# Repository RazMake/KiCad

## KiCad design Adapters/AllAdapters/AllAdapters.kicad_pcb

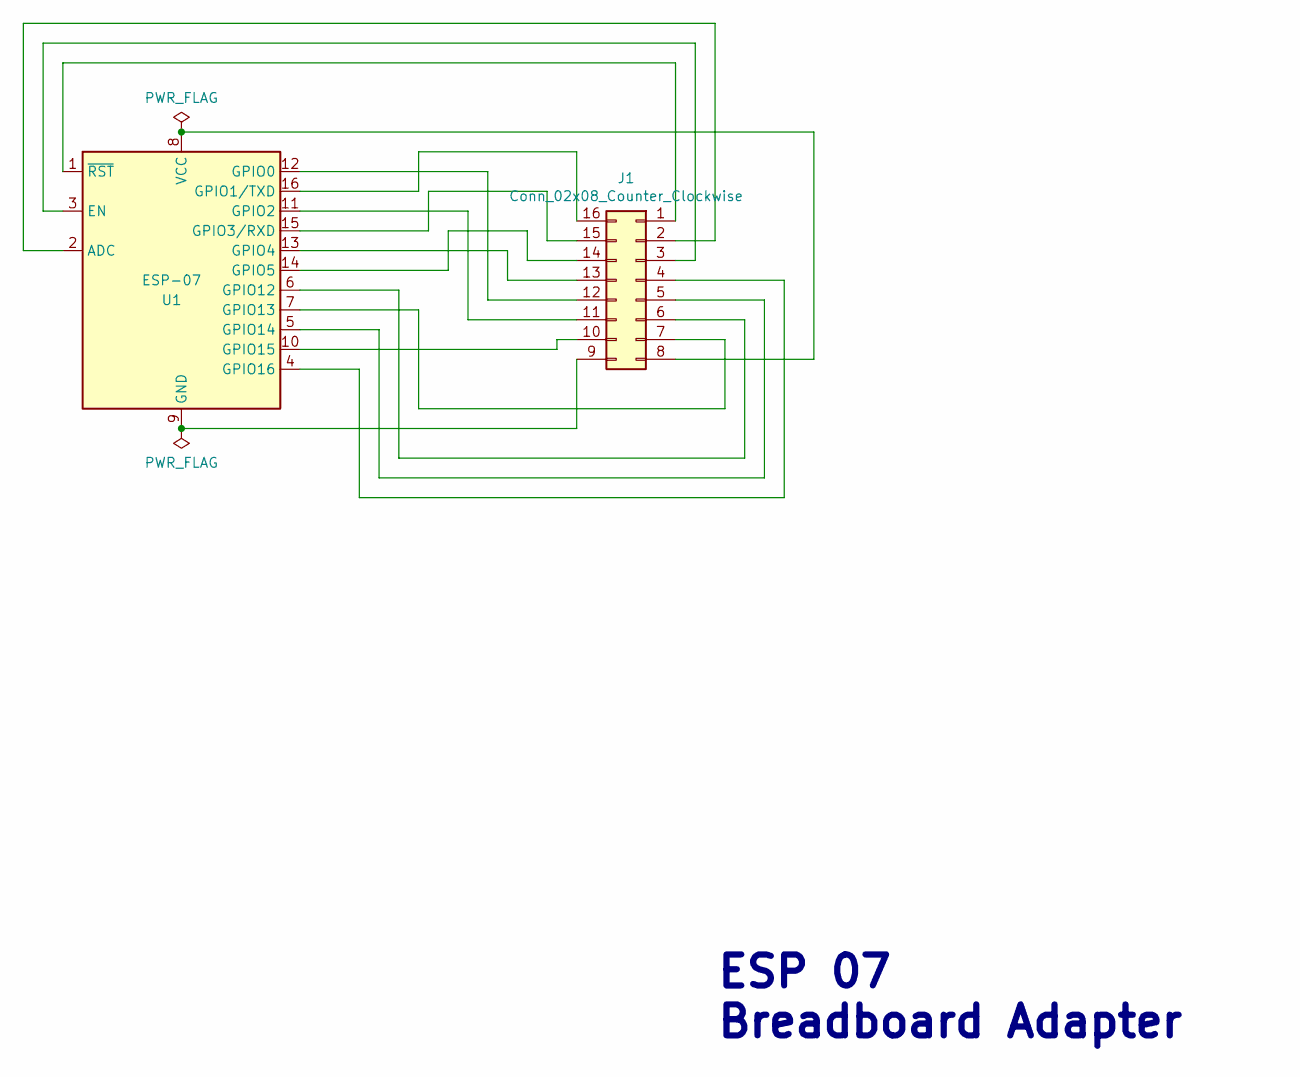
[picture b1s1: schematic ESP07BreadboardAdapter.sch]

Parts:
J1: Conn_02x08_Counter_Clockwise; ESP07BreaboardSocket
U1: ESP-07; ESP-07Socket

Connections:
unnamed: J1.1, U1.1 (~RST)
unnamed: J1.2, U1.2 (ADC)
unnamed: J1.3, U1.3 (EN)
unnamed: J1.4, U1.4 (GPIO16)
unnamed: J1.5, U1.5 (GPIO14)
unnamed: J1.6, U1.6 (GPIO12)
unnamed: J1.7, U1.7 (GPIO13)
unnamed: J1.8, U1.8 (VCC)
unnamed: J1.9, U1.9 (GND)
unnamed: J1.10, U1.10 (GPIO15)
unnamed: J1.11, U1.11 (GPIO2)
unnamed: J1.12, U1.12 (GPIO0)
unnamed: J1.13, U1.13 (GPIO4)
unnamed: J1.14, U1.14 (GPIO5)
unnamed: J1.15, U1.15 (GPIO3/RXD)
unnamed: J1.16, U1.16 (GPIO1/TXD)

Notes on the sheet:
ESP 07 Breadboard Adapter

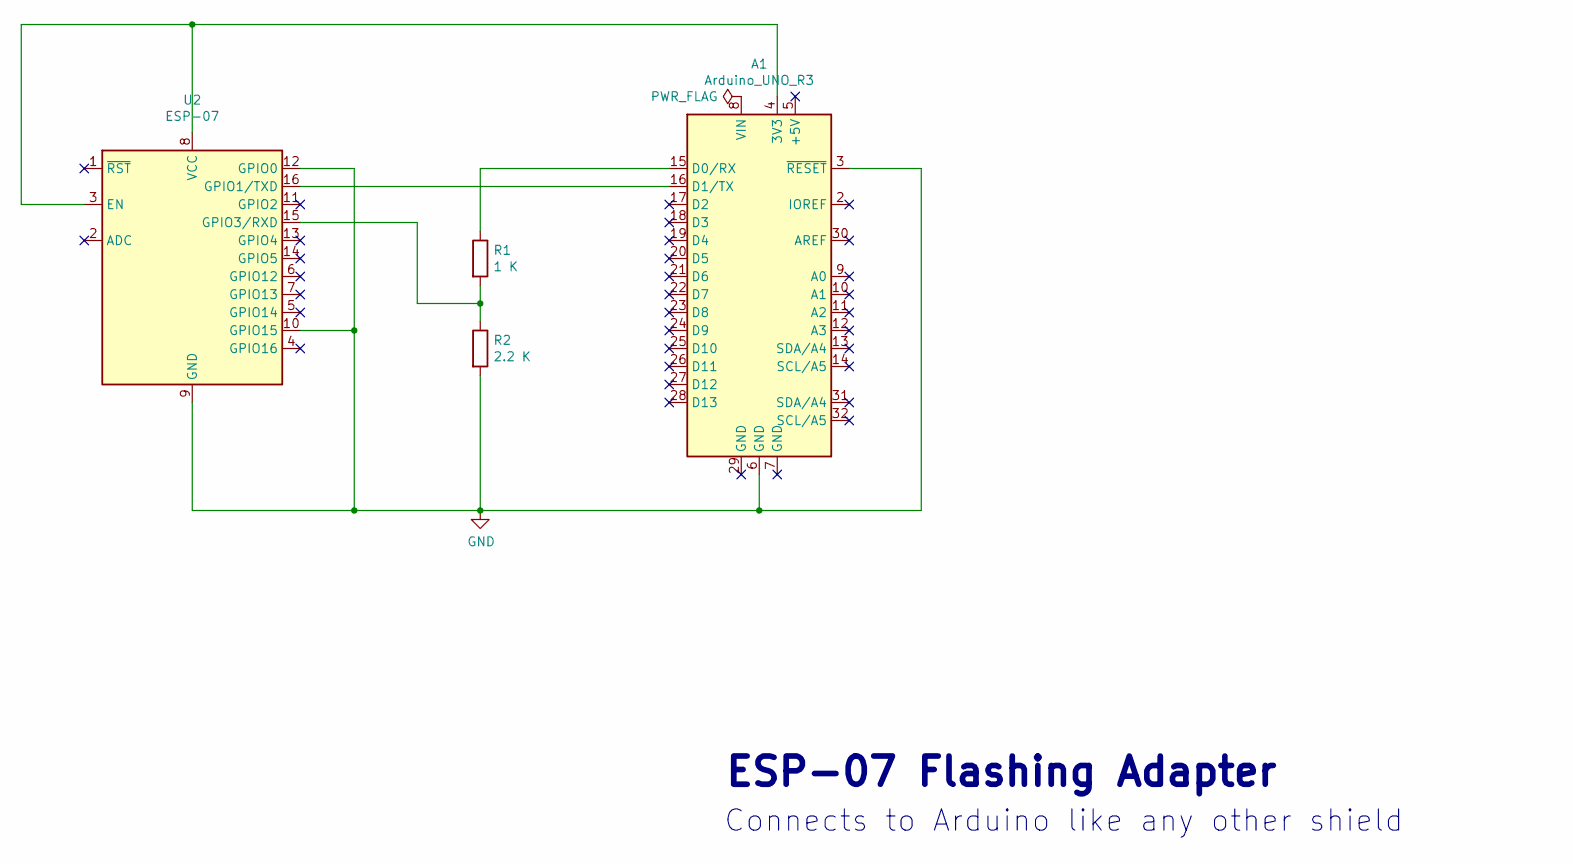
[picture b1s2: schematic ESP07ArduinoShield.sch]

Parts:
A1: Arduino_UNO_R3; Arduino_UNO_R3_Headers
R1: 1 K; R_Axial_DIN0204_L3.6mm_D1.6mm_P5.08mm_Horizontal
R2: 2.2 K; R_Axial_DIN0204_L3.6mm_D1.6mm_P5.08mm_Horizontal
U2: ESP-07; ESP07BreaboardSocket

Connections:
GND: A1.3 (~RESET), A1.6 (GND), R2.2, U2.9 (GND), U2.10 (GPIO15), U2.12 (GPIO0)
unnamed: A1.4 (3V3), U2.3 (EN), U2.8 (VCC)
unnamed: A1.15 (D0/RX), R1.1
unnamed: A1.16 (D1/TX), U2.16 (GPIO1/TXD)
unnamed: R1.2, R2.1, U2.15 (GPIO3/RXD)

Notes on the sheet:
ESP-07 Flashing Adapter
Connects to Arduino like any other shield

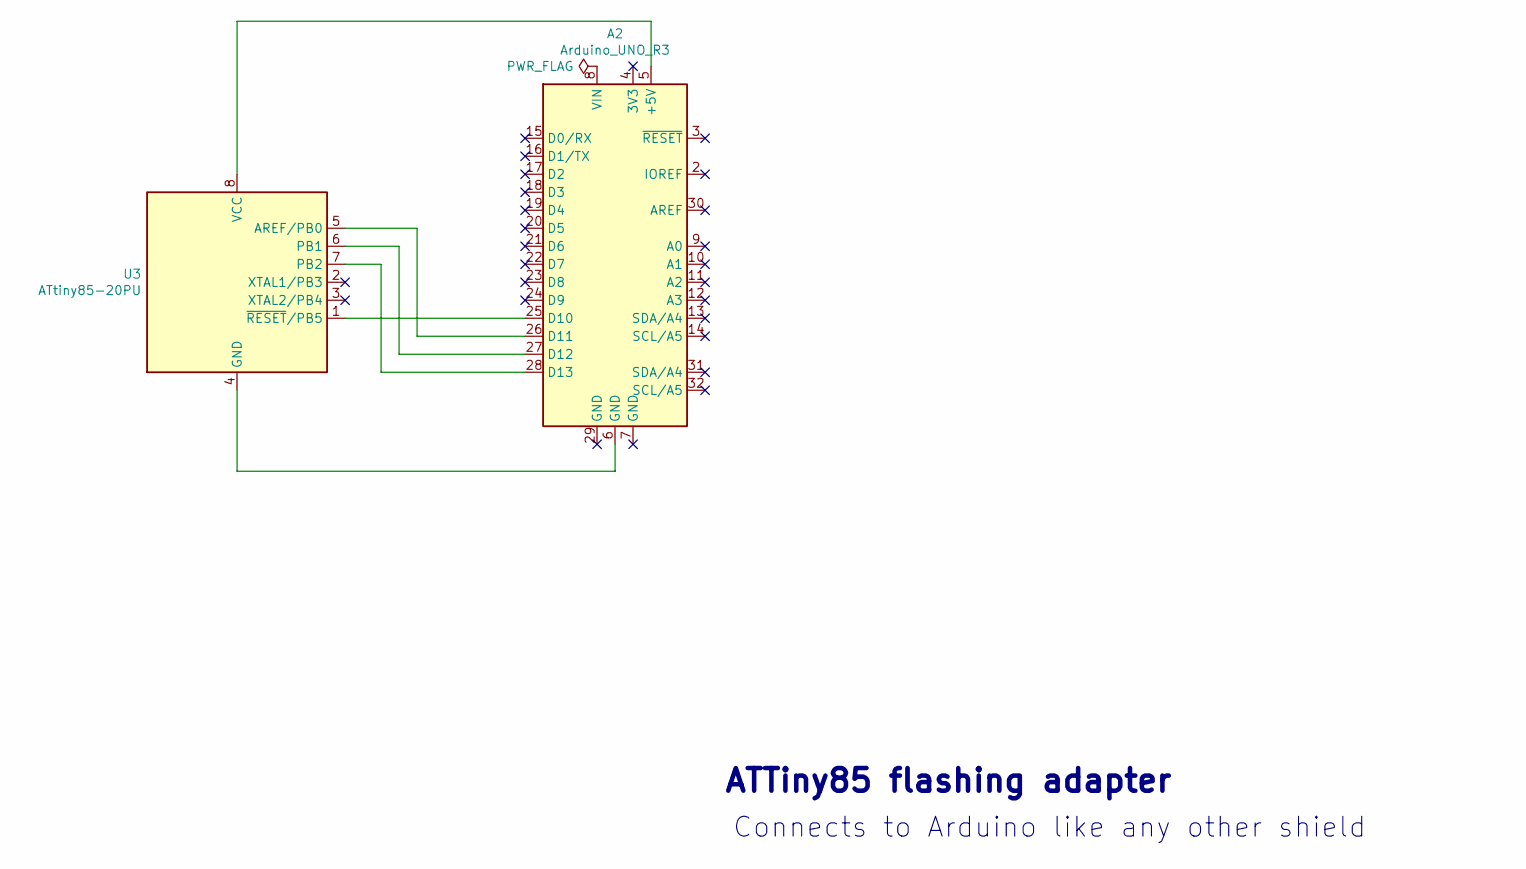
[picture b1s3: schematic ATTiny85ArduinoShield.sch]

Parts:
A2: Arduino_UNO_R3; Arduino_UNO_R3_Headers
U3: ATtiny85-20PU; DIP-8_W7.62mm

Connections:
unnamed: A2.5 (+5V), U3.8 (VCC)
unnamed: A2.6 (GND), U3.4 (GND)
unnamed: A2.25 (D10), U3.1 (~RESET~/PB5)
unnamed: A2.26 (D11), U3.5 (AREF/PB0)
unnamed: A2.27 (D12), U3.6 (PB1)
unnamed: A2.28 (D13), U3.7 (PB2)

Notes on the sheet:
ATTiny85 flashing adapter
Connects to Arduino like any other shield

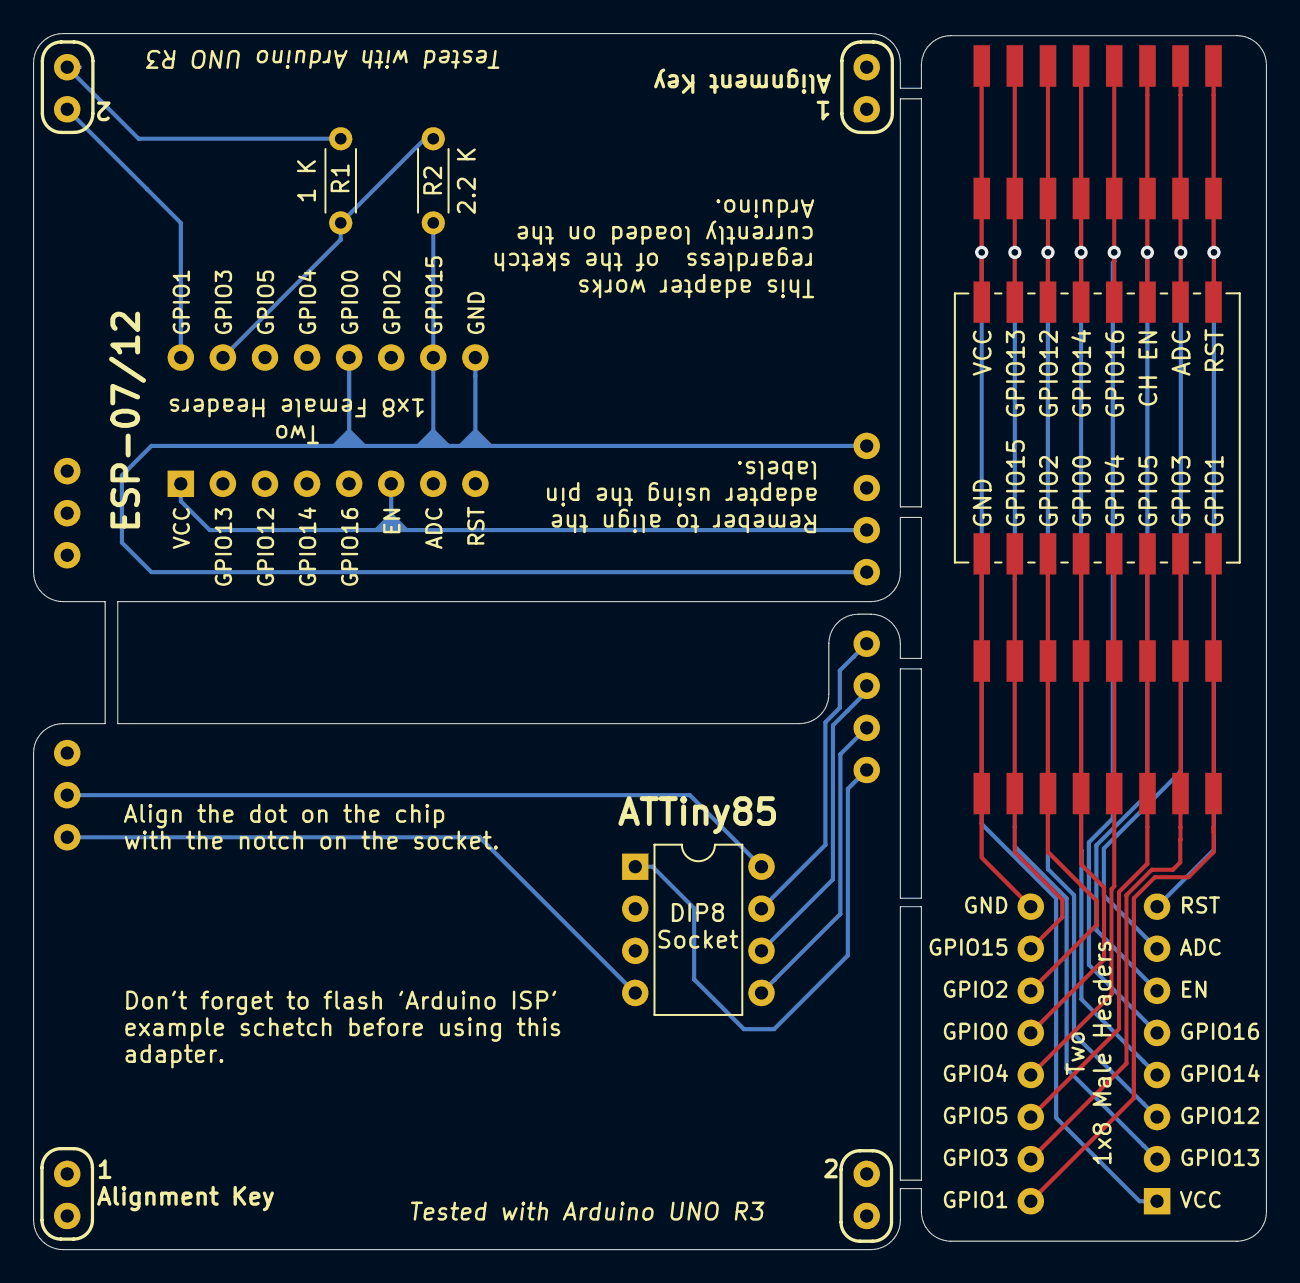
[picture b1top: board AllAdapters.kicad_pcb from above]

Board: 2 copper layers, 74.4 x 73.4 mm, 8 parts (0 on the bottom side), 27 nets.

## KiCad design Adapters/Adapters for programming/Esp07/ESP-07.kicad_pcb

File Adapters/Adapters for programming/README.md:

# Contents
This folder contains KiCad projects for PCBs used for connecting various microcontrollers to an Arduino UNO R3 ([~$3](https://www.banggood.com/Geekcreit-UNO-R3-ATmega328P-Development-Board-For-No-Cable-p-964163.html?rmmds=search&cur_warehouse=CN) 
proto board).  
The Arduino UNO board is then connected to a computer  for [flashing new firmware](https://github.com/RazMake/ArduinoUNOMultiProgrammer/blob/master/README.md) on them.
* **[ESP07](https://github.com/RazMake/KiCad/tree/master/Adapters/Adapters%20for%20programming/Esp07)** - PCB that adapts an ESP07 chip to Arduino UNO R3 headers.  
     *(this also includes the *Gerber* files, for ordering the PCB. Board size: **53** x **48**mm / **2.11** x **1.9** in)*
* **[ATTiny85](https://github.com/RazMake/KiCad/tree/master/Adapters/Adapters%20for%20programming/ATTiny85)** - PCB that adapts an ATTiny85 chip to Arduino UNO R3 headers.  
     *(this also includes the *Gerber* files, for ordering the PCB. Board size: **53** x **49**mm / **2.1** x **1.94** in)*

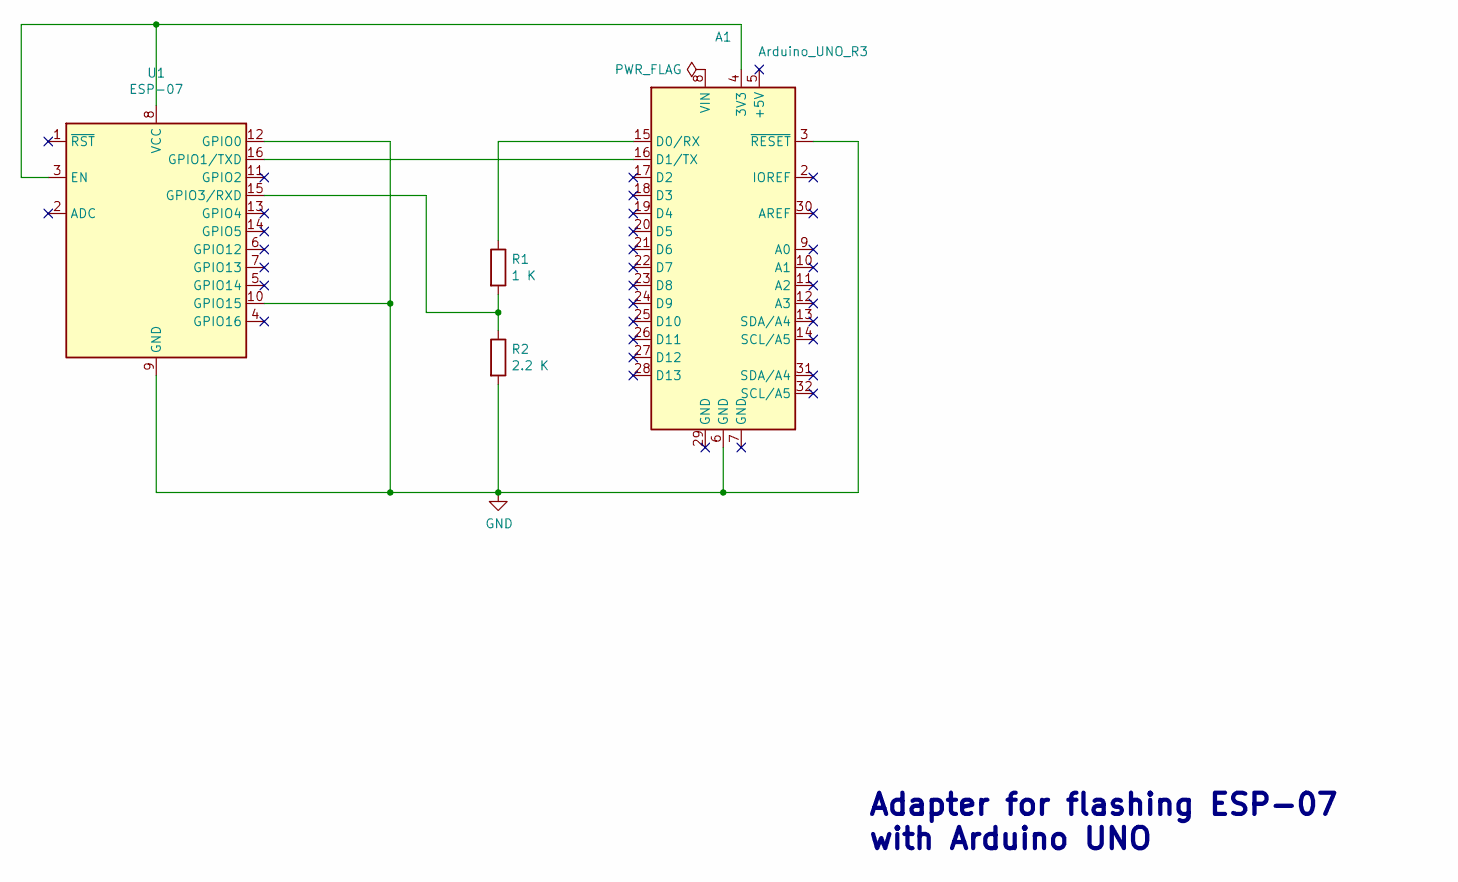
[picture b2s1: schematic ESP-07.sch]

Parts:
A1: Arduino_UNO_R3; Arduino_UNO_R3_Headers
R1: 1 K; R_Axial_DIN0204_L3.6mm_D1.6mm_P5.08mm_Horizontal
R2: 2.2 K; R_Axial_DIN0204_L3.6mm_D1.6mm_P5.08mm_Horizontal
U1: ESP-07; ESP07BreaboardSocket

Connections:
GND: A1.3 (~RESET), A1.6 (GND), R2.2, U1.9 (GND), U1.10 (GPIO15), U1.12 (GPIO0)
unnamed: A1.4 (3V3), U1.3 (EN), U1.8 (VCC)
unnamed: A1.15 (D0/RX), R1.1
unnamed: A1.16 (D1/TX), U1.16 (GPIO1/TXD)
unnamed: R1.2, R2.1, U1.15 (GPIO3/RXD)

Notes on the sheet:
Adapter for flashing ESP-07 with Arduino UNO

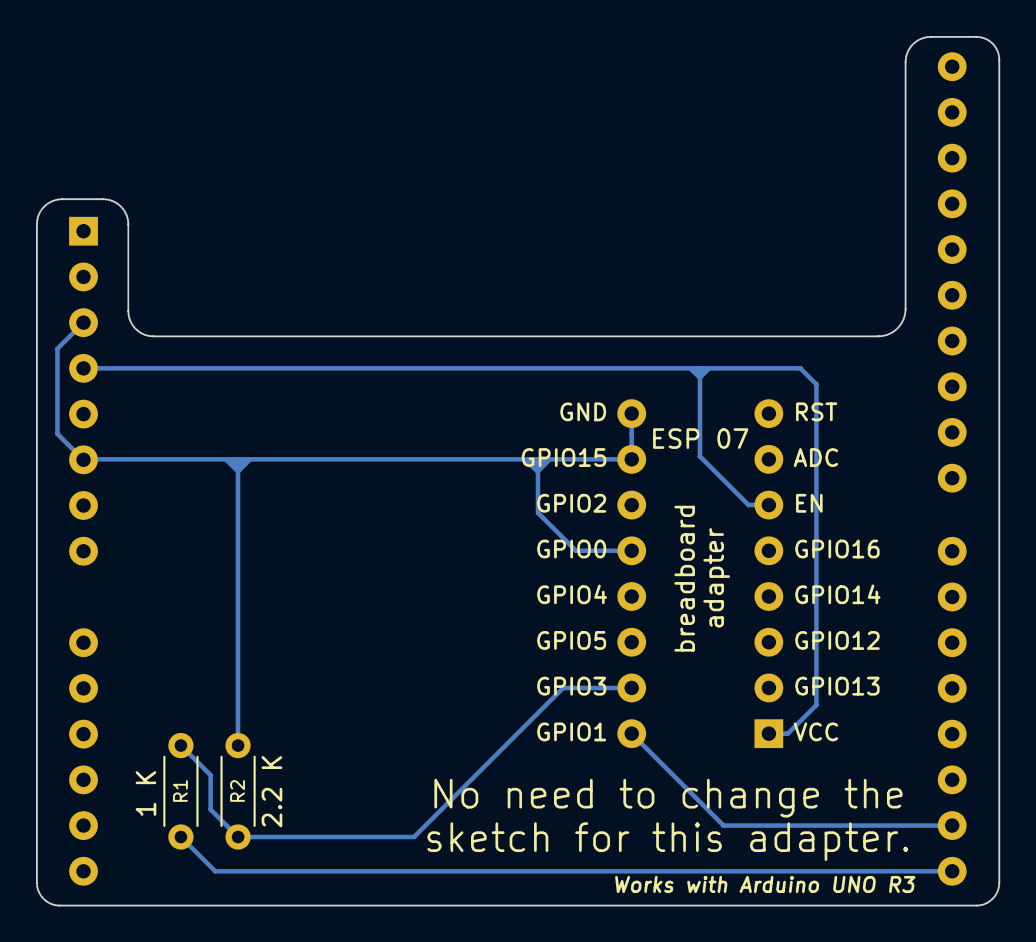
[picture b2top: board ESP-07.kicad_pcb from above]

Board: 2 copper layers, 53.5 x 48.3 mm, 4 parts (0 on the bottom side), 5 nets.

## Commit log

2020-02-23 First adapter: ESP07 to breadboard, V2
2020-02-23 Added readme with some description for each project
2020-02-23 Adding gitignore, to skip cache and backup files
2020-02-23 Delete fp-info-cache
    Remove cache file
2020-02-23 Remove backups and cache files
2020-02-23 Removed some more cache files
2020-02-23 Adding readme for the flash adapters folder
2020-02-23 Added Gerber files for Attiny85 adapter, fixed gitignore file
2020-02-23 Updated the readme file
2020-02-23 Added the breadboard form of the ESP connector. Re-generated the Gerber for the adapter
2020-02-23 Fixed error in ESP breadboard adapter footprint, updated the schema to wire the for the new layout. Updated the ESP flashing adapter.
2020-02-23 Signed all the boards, and re-generated the Gerber files
2020-02-23 Minor updates to readme files.
2020-02-25 Fixed schematic for ESP adapter and regenerated Gerber files
2020-02-25 Updated dimensions after ordering the boards
2020-04-05 Updated all adapters project and adding the schematics for ESP07 running
2020-04-05 Moving the schemas to their own folder
